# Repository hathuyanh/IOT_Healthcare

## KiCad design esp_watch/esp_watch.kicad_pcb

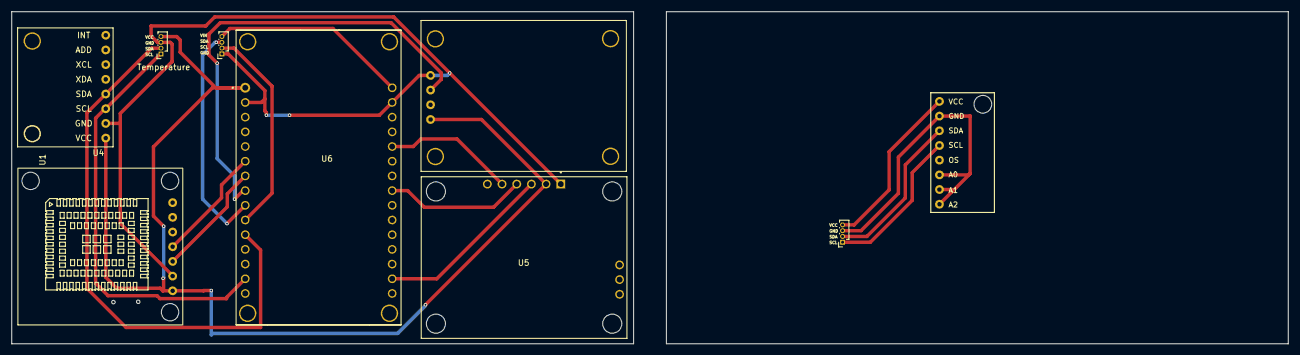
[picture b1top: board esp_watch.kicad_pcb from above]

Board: 2 copper layers, 220.7 x 57.4 mm, 8 parts (0 on the bottom side), 10 nets.

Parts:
HEART RATE: PinSocket_1x04_P1.00mm_Vertical
HEART RATE#2: PinSocket_1x04_P1.00mm_Vertical
Temperature: PinSocket_1x04_P1.00mm_Vertical
U1: SIM 7670
U2: NEO_6M
U4: module_mpu6050
U5: SEN-12650; MODULE_SEN-12650
U6: ESP32-DEVKIT-V1; MODULE_ESP32_DEVKIT_V1

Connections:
GND: HEART RATE#2.1, Temperature.3, U4.2 (GND), U5.JP3_1 (GND), U6.2 (GND), U6.29 (GND)
unnamed: HEART RATE#2.4, U6.30 (VIN)
unnamed: HEART RATE#2.3, U6.9 (D18)
unnamed: HEART RATE#2.2, U6.10 (D19)
unnamed: Temperature.1, U4.3 (SCL), U6.14 (D22)
unnamed: Temperature.2, U4.4 (SDA), U6.11 (D21)
unnamed: U5.JP3_5 (LO+), U6.26 (D14)
unnamed: U5.JP3_4 (LO-), U6.23 (D25)
unnamed: U5.JP3_3 (SIGNAL_OUT), U6.17 (VP)
VCC: Temperature.4, U4.1 (VCC), U5.JP3_2 (3.3V), U6.1 (3V3)

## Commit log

2024-10-16 Add main code file
2024-10-16 Add libraries files
2024-10-17 Add circuit schematic
2024-11-02 Add pin connection diagram
2025-01-20 Upload PCB designing file
